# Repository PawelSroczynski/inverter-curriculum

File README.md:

# From Zero Electronics to Community Energy Independence

**Build droop-controlled inverters. Connect them into a tiered AC swarm grid.**

Learn electronics from scratch, build 6-15kW inverters, connect them into a self-organizing microgrid that powers your whole community—no utility required.

---

## Why Build This?

| Problem | This Project |
|---------|--------------|
| Commercial inverters cost $3,000+ each | Build for ~$775 per unit |
| Proprietary systems, no repair possible | Open source, fully repairable |
| Single inverter = single point of failure | Swarm shares load automatically |
| Grid dependency | Complete energy independence |
| Complex microgrid controllers | Self-organizing via droop control |

**End Goal:** 12-household swarm microgrid with 72kW capacity, tiered AC buses, automatic power sharing between clusters.

---

## System Architecture

The system uses a **tiered AC bus** design: each cluster has its own internal bus, and clusters connect through a separate swarm bus via gateways. This means only 3 gateways need to sync—not 12 inverters.

---

### Level 1: Tiered Bus Overview

```
┌──────────────────────────────────────────────────────────────────────────────────────┐
│                              SWARM BUS (1000m backbone)                              │
│                                                                                      │
│      ════════════════════════════════════════════════════════════════════════        │
│           │                         │                         │                      │
│      ┌────┴────┐               ┌────┴────┐               ┌────┴────┐                │
│      │GATEWAY A│               │GATEWAY B│               │GATEWAY C│                │
│      │Contactor│               │Contactor│               │Contactor│                │
│      │  ESP32  │               │  ESP32  │               │  ESP32  │                │
│      └────┬────┘               └────┬────┘               └────┬────┘                │
│           │                         │                         │                      │
│      ═════╪═════               ═════╪═════               ═════╪═════                │
│      CLUSTER A                 CLUSTER B                 CLUSTER C                  │
│      INTERNAL BUS              INTERNAL BUS              INTERNAL BUS               │
│      (80m)                     (80m)                     (80m)                       │
│           │                         │                         │                      │
│      ┌────┼────┐               ┌────┼────┐               ┌────┼────┐                │
│      │    │    │               │    │    │               │    │    │                │
│     H1   H2   H3  H4          H5   H6   H7  H8          H9  H10  H11 H12            │
│     INV  INV  INV INV         INV  INV  INV INV         INV  INV  INV INV           │
│                                                                                      │
│    ◄──────────────────────── 1000m total site ───────────────────────────►          │
│                                                                                      │
│    KEY BENEFIT: Only 3 gateways sync on swarm bus, not 12 inverters                 │
│                                                                                      │
│    TWO LEVELS OF DROOP:                                                             │
│    • Within cluster: 4 inverters share via droop on internal bus                    │
│    • Between clusters: 3 gateways share via droop on swarm bus                      │
│                                                                                      │
└──────────────────────────────────────────────────────────────────────────────────────┘
```

---

### Self-Reliance Levels

The system operates in 4 modes, from most isolated to most connected:

```
┌──────────────────────────────────────────────────────────────────────────────────────┐
│  LEVEL 1: HOUSE SELF-RELIANT (99% of time)                                          │
│                                                                                      │
│    House 1: [Solar] → [Battery] → [Inverter] → [Loads]                              │
│             Own production covers own consumption                                    │
│             No power flows to/from cluster bus                                       │
│                                                                                      │
├──────────────────────────────────────────────────────────────────────────────────────┤
│  LEVEL 2: CLUSTER SELF-RELIANT (swarm disconnected)                                 │
│                                                                                      │
│    Cluster A: H1 ←→ H2 ←→ H3 ←→ H4                                                  │
│               Sharing within cluster via droop                                       │
│               Gateway contactor: OPEN (isolated from swarm)                          │
│                                                                                      │
│    Use case: Swarm bus fault, or cluster has enough internal capacity               │
│                                                                                      │
├──────────────────────────────────────────────────────────────────────────────────────┤
│  LEVEL 3: CLUSTER NEEDS HELP (normal swarm operation)                               │
│                                                                                      │
│    Cluster A (depleted) ←── power ←── Cluster B (surplus)                           │
│                                             │                                        │
│    Gateway A closes contactor when:         │                                        │
│    • Cluster A frequency drops (heavy load) │                                        │
│    • Swarm frequency is higher (others OK)  │                                        │
│    • Frequencies match within ±0.5Hz        │                                        │
│                                                                                      │
├──────────────────────────────────────────────────────────────────────────────────────┤
│  LEVEL 4: HOUSE NEEDS HELP (within cluster)                                         │
│                                                                                      │
│    H1 (heavy load, e.g. EV) ←── power ←── H2, H3, H4 (light loads)                  │
│                                                                                      │
│    Via droop physics on cluster internal bus                                         │
│    No gateway involved - stays within cluster                                        │
│                                                                                      │
└──────────────────────────────────────────────────────────────────────────────────────┘
```

---

### Inter-Cluster Power Flow

How power moves from House 11 (Cluster C) to House 1 (Cluster A):

```
    H11 Inverter (50.0 Hz, light load)
            │
            ↓ power flows
    Cluster C Internal Bus
            │
            ↓
    Gateway C (contactor closed)
            │
            ↓
    ═══════ SWARM BUS ═════════════════════════════
            │
            ↓
    Gateway A (contactor closed)
            │
            ↓
    Cluster A Internal Bus (49.5 Hz, heavy load)
            │
            ↓ power flows
    H1 Inverter
            │
            ↓
    H1 Loads (kettle, EV, etc.)

    5 HOPS, PURE PHYSICS:
    No direct communication between H1 and H11.
    Power flows automatically from high frequency (surplus)
    to low frequency (deficit) via droop control.
```

---

### Gateway Sync Logic

Each gateway monitors both bus frequencies and decides when to connect:

```
    ┌─────────────────────────────────────────────────────────────────┐
    │  GATEWAY DECISION FLOWCHART                                     │
    │                                                                 │
    │  [Measure cluster frequency] → f_cluster                        │
    │  [Measure swarm frequency]   → f_swarm                          │
    │                                                                 │
    │  IF |f_cluster - f_swarm| < 0.5 Hz:                             │
    │      → CLOSE contactor (safe to connect)                        │
    │                                                                 │
    │  ELSE IF f_cluster < f_swarm - 0.5:                             │
    │      → Cluster needs power, wait for freq match                 │
    │                                                                 │
    │  ELSE IF f_cluster > f_swarm + 0.5:                             │
    │      → Cluster has surplus, wait for freq match                 │
    │                                                                 │
    │  IF f_cluster < 47.5 Hz:                                        │
    │      → EMERGENCY: cluster critically low                        │
    │      → Force close (accept brief surge)                         │
    │                                                                 │
    └─────────────────────────────────────────────────────────────────┘
```

---

### Level 2: Cluster Internal Detail

Each house is self-reliant with 6-15kW inverter. Load-balancing only kicks in for special scenarios.

```
┌──────────────────────────────────────────────────────────────────────────────────────┐
│                      CLUSTER - NORMAL OPERATION (99% of the time)                    │
│                                                                                      │
│   HOUSE 1                  HOUSE 2                  HOUSE 3                          │
│   ┌──────────────────┐     ┌──────────────────┐     ┌──────────────────┐            │
│   │ Solar 6kW        │     │ Solar 6kW        │     │ Solar 6kW        │            │
│   │ Bat 15kWh        │     │ Bat 15kWh        │     │ Bat 15kWh        │            │
│   │ Inv 6kW          │     │ Inv 6kW          │     │ Inv 6kW          │            │
│   │                  │     │                  │     │                  │            │
│   │ BATTERY 48V      │     │ BATTERY 48V      │     │ BATTERY 48V      │            │
│   │      │           │     │      │           │     │      │           │            │
│   │      ▼           │     │      ▼           │     │      ▼           │            │
│   │ INVERTER 50.0Hz  │     │ INVERTER 50.0Hz  │     │ INVERTER 50.0Hz  │            │
│   │      │           │     │      │           │     │      │           │            │
│   │      ▼           │     │      ▼           │     │      ▼           │            │
│   │ LOADS 2kW        │     │ LOADS 4kW        │     │ LOADS 1kW        │            │
│   │ (fridge,lights)  │     │ (oven,fridge)    │     │ (lights,TV)      │            │
│   └────────┼─────────┘     └────────┼─────────┘     └────────┼─────────┘            │
│            │                        │                        │                      │
│   ─────────┴────────────────────────┴────────────────────────┴───────────────►      │
│   230V AC BUS @ 50.0 Hz - NO POWER FLOWING BETWEEN HOUSES (each self-sufficient)    │
│   ──────────────────────────────────────────────────────────────────► to cluster    │
│                                                                                      │
│            │ RJ45                   │ RJ45                   │ RJ45                 │
│   ─────────○───────────────────────○───────────────────────○────────► to cluster   │
│   CAN BUS: sync timing + SOC% + status data                                         │
│                                                                                      │
│   NORMAL: Each 6kW inverter handles its own loads easily (oven=3kW, fridge=200W)    │
│                                                                                      │
└──────────────────────────────────────────────────────────────────────────────────────┘

┌──────────────────────────────────────────────────────────────────────────────────────┐
│                  CLUSTER - SPECIAL SCENARIO: EV CHARGING EXCEEDS 6kW                 │
│                                                                                      │
│   HOUSE 1                  HOUSE 2 (needs help!)   HOUSE 3                          │
│   ┌──────────────────┐     ┌──────────────────┐     ┌──────────────────┐            │
│   │ Inv 6kW          │     │ Inv 6kW (MAXED)  │     │ Inv 6kW          │            │
│   │                  │     │                  │     │                  │            │
│   │ BATTERY 48V      │     │ BATTERY 48V      │     │ BATTERY 48V      │            │
│   │      │           │     │      │           │     │      │           │            │
│   │      ▼ 2kW       │     │      ▼ 6kW MAX   │     │      ▼ 1.5kW     │            │
│   │ INVERTER 50.0Hz  │     │ INVERTER 49.7Hz  │     │ INVERTER 49.9Hz  │            │
│   │      │           │     │      │           │     │      │           │            │
│   │      ▼           │     │      ▼           │     │      ▼           │            │
│   │ LOADS 1kW        │     │ LOADS 7kW !!!    │     │ LOADS 1kW        │            │
│   │                  │     │ (EV charger)     │     │                  │            │
│   └────────┼─────────┘     └────────┼─────────┘     └────────┼─────────┘            │
│            │                        │                        │                      │
│   ─────────┴────────────────────────┴────────────────────────┴───────────────►      │
│                                                                                      │
│            ════1.0kW═══════════════►║◄════════0.5kW══════════                       │
│                    House 1 pushes   ║   House 3 pushes                              │
│                                                                                      │
│   230V AC BUS @ 49.85 Hz - POWER FLOWS TO HOUSE 2 (droop triggered)                 │
│   ──────────────────────────────────────────────────────────────────► to cluster    │
│                                                                                      │
├──────────────────────────────────────────────────────────────────────────────────────┤
│   WHY LOAD-BALANCING KICKS IN:                                                      │
│                                                                                      │
│   House 2 plugs in EV charger (7kW) but inverter maxes at 6kW:                       │
│   • Inverter strains → frequency drops to 49.7 Hz                                   │
│   • House 1 & 3 see low freq → push power to bus                                    │
│   • House 2 gets: 6kW local + 1kW from H1 + 0.5kW from H3 = 7.5kW available         │
│                                                                                      │
│   OTHER SCENARIOS THAT TRIGGER SHARING:                                             │
│   • Low battery (BMS limits output) → neighbors supply deficit                      │
│   • Inverter fault/maintenance → house runs entirely from bus                       │
│   • Motor startup surge (9kW for 2 sec) → cluster absorbs spike                     │
│                                                                                      │
└──────────────────────────────────────────────────────────────────────────────────────┘
```

---

### Level 3: House Detail

Internal wiring of one house, showing connection to cluster AC bus.

```
┌────────────────────────────────────────────────────────────────────────────────────┐
│                              HOUSE (typical)                                       │
│                                                                                    │
│   ROOF                                                                             │
│   ┌──────────────────┐                                                             │
│   │   Solar Panels   │                                                             │
│   │      3kW         │                                                             │
│   └────────┬─────────┘                                                             │
│            │ DC (Vmp ~100V)                                                        │
│            ▼                                                                       │
│   ┌──────────────────┐                                                             │
│   │   MPPT Charger   │                                                             │
│   │  (Libre Solar)   │                                                             │
│   └────────┬─────────┘                                                             │
│            │ 48V DC                                                                │
│            ▼                                                                       │
│   ┌──────────────────┐                                                             │
│   │       BMS        │   48V DC stays inside this house                            │
│   │   48V / 15kWh    │   (no DC connection to other houses)                        │
│   │    LiFePO4       │                                                             │
│   └────────┬─────────┘                                                             │
│            │ 48V DC                                                                │
│            ▼                                                                       │
│   ┌──────────────────┐              ┌──────────────────────────────────────────┐   │
│   │    INVERTER      │     RJ45     │                                          │   │
│   │      6kW         │◄────────────►│  CAN BUS                                 │   │
│   │    EG8010        │              │  ◄───── to/from other houses + clusters  │   │
│   │    ESP32         │              └──────────────────────────────────────────┘   │
│   │    MCP2515       │                                                             │
│   │  (MASTER/SLAVE)  │                                                             │
│   └────────┬─────────┘                                                             │
│            │ 230V AC                                                               │
│            ▼                                                                       │
│   ┌──────────────────┐              ┌──────────────────────────────────────────┐   │
│   │   MAIN BREAKER   │    63A MCB   │                                          │   │
│   │   (house entry)  │◄────────────►│  230V AC CLUSTER BUS                     │   │
│   └────────┬─────────┘              │  ◄───── to/from other houses + clusters  │   │
│            │                        └──────────────────────────────────────────┘   │
│            │                                                                       │
│   ═════════╧═══════════════════════════════════════════════════════════            │
│   ║            230V AC HOUSE DISTRIBUTION BOARD                    ║               │
│   ══════╤══════════╤══════════╤══════════╤══════════╤══════════════                │
│         │          │          │          │          │                              │
│      ┌──┴──┐    ┌──┴──┐    ┌──┴──┐    ┌──┴──┐    ┌──┴──┐                          │
│      │ 6A  │    │ 10A │    │ 16A │    │ 16A │    │ 20A │                          │
│      │Light│    │Fridge│   │Plugs│    │Plugs│    │Oven │                          │
│      │ MCB │    │ MCB │    │ MCB │    │ MCB │    │ MCB │                          │
│      └──┬──┘    └──┬──┘    └──┬──┘    └──┬──┘    └──┬──┘                          │
│         │          │          │          │          │                              │
│         ▼          ▼          ▼          ▼          ▼                              │
│      Lights     Fridge     Kitchen    Living     Oven                              │
│                            plugs      plugs                                        │
│                                                                                    │
│   CONNECTION DETAIL: How House Connects to Cluster                                 │
│   ┌────────────────────────────────────────────────────────────────────────────┐   │
│   │                                                                            │   │
│   │    230V AC CLUSTER BUS (shared with other houses)                          │   │
│   │    ═══════════════╤═══════════════════════════════════════                 │   │
│   │                   │                                                        │   │
│   │              ┌────┴────┐                                                   │   │
│   │              │  63A    │  Main breaker: isolates house from cluster        │   │
│   │              │ BREAKER │  if fault or maintenance                          │   │
│   │              └────┬────┘                                                   │   │
│   │                   │                                                        │   │
│   │    ═══════════════╧═══════════════════════════════════════                 │   │
│   │    230V AC HOUSE DISTRIBUTION (internal to this house)                     │   │
│   │                                                                            │   │
│   │    Power flows BOTH directions:                                            │   │
│   │    • House produces excess → pushes to cluster bus → other houses use it   │   │
│   │    • House needs more → pulls from cluster bus → other houses supply it    │   │
│   │                                                                            │   │
│   │    ONLY TWO CONNECTIONS LEAVE THIS HOUSE:                                  │   │
│   │    1. 230V AC (L + N + PE) → to cluster AC bus                             │   │
│   │    2. CAN bus (RJ45) → to other houses for communication                   │   │
│   │                                                                            │   │
│   │    48V DC stays entirely inside the house (battery is isolated)            │   │
│   │                                                                            │   │
│   └────────────────────────────────────────────────────────────────────────────┘   │
│                                                                                    │
└────────────────────────────────────────────────────────────────────────────────────┘
```

---

### Hardware Summary

**Per House (isolated 48V DC system):**
| Component | Description |
|-----------|-------------|
| Solar Panels | 3kW array (size varies) |
| MPPT Charger | Libre Solar MPPT-2420-HC or similar |
| BMS + Battery | Libre Solar BMS-C1 + 48V/15kWh LiFePO4 (stays inside house) |
| Inverter | OzInverter 6kW with EG8010 + ESP32 + MCP2515 |
| Main Breaker | 63A MCB, isolates house from cluster AC bus |
| RJ45 Jack | CAN bus connection to other houses |

**Per Cluster (shared between houses):**
| Component | Description |
|-----------|-------------|
| 230V AC Bus | 4mm² cable connecting all house inverter outputs (10-30m) |
| CAN Bus | RJ45 cables daisy-chaining all houses (10-30m runs) |

**Per Gateway (connects cluster to swarm bus):**
| Component | Description |
|-----------|-------------|
| Gateway ESP32 | Monitors both bus frequencies, controls contactor |
| Contactor 63A | Connects/disconnects cluster from swarm bus |
| Voltage sensors | Measures cluster and swarm bus frequencies |

**Swarm Bus (between clusters):**
| Component | Description |
|-----------|-------------|
| 5-Wire Cable | L + N + PE (4mm²) + CAN-H + CAN-L (0.5mm²) |
| Distance | 200-400m between gateways |

---

### How It Works

**Power Flow (tiered):**
1. Sun → Solar panels → MPPT → Battery (48V DC, inside house)
2. Battery → Inverter → 230V AC → House loads
3. Excess → Cluster internal bus → Other houses in cluster (via droop)
4. Still excess → Gateway → Swarm bus → Other clusters (via droop)

**No DC Bus Between Houses:**
- Each house has isolated 48V battery (simpler, cheaper wiring)
- Power sharing happens via 230V AC (thinner cables for same power)
- Battery balancing is indirect: low battery house draws from AC, others supply

**Communication:**
1. ESP32 master broadcasts sync timing @ 100Hz on CAN bus
2. All slave ESP32s adjust their EG8010 phase to match
3. Status messages (SOC%, load, faults) shared via ThingSet protocol

**Droop Control (automatic power sharing):**
- Heavy load → inverter frequency drops slightly (e.g., 50.0 → 49.8 Hz)
- Other inverters sense lower frequency → push more power
- No central controller needed - physics handles balancing

```
How Droop Control Shares Power Between Houses (EV Charging Example):

  House 2 (charging EV at 7kW)           House 1 (light load - 1kW)
  ┌─────────────────────────────┐        ┌─────────────────────────────┐
  │  6kW inverter (maxed out)   │        │  6kW inverter (idle)        │
  │                             │        │                             │
  │  Battery ──► Inverter ──┬──►│ EV     │  Battery ──► Inverter ──┬──►│ load
  │    48V        6kW       │   │ 7kW    │    48V        2kW       │   │ 1kW
  │              49.7 Hz    │   │        │              50.0 Hz    │   │
  └─────────────────────────┼───┘        └─────────────────────────┼───┘
                            │                                      │
                ◄═══════════╧══════════════════════════════════════╧═══
                230V AC BUS - House 1 pushes 2kW → House 2 (freq settles at 49.85 Hz)

  WHY THIS TRIGGERS SHARING (with 6kW inverters):
  • House 2 needs 7kW but its inverter maxes out at 6kW
  • Inverter strains → frequency drops to 49.7 Hz
  • House 1 sees low freq → pushes power to help

  1. House 2 plugs in EV charger (7kW) → inverter hits 6kW limit → freq drops
  2. House 1 inverter sees 49.7 Hz → increases output → pushes power to bus
  3. Power flows: House 1 battery → inverter → AC bus → House 2 EV
  4. System settles at 49.85 Hz with 7kW delivered

  The math for House 2:
  • EV charger needs:         7.0 kW
  • Local 6kW inverter maxed: 6.0 kW (can't do more)
  • AC bus supplies:          1.0 kW (from House 1)
  • House 1 also powers own:  1.0 kW load
  • House 1 total output:     2.0 kW (1kW local + 1kW to bus)

  Key: Single inverter can't do 7kW, but cluster of two 6kW inverters can.
       Droop control automatically shares the load - no manual switching.
```

---

### When AC Bus Power Sharing Kicks In

With 6-15kW inverters, normal household loads won't trigger sharing. The real value is resilience:

```
┌─────────────────────────────────────────────────────────────────────────────┐
│  SCENARIO 1: Low Battery Protection                                        │
│                                                                             │
│  House 2: SOC at 15% → BMS limits discharge to 1kW                          │
│  House 2 load: 3kW (fridge + pump + lights)                                 │
│  ───────────────────────────────────────────────────────────────            │
│  House 1 & 3 push 2kW through AC bus → House 2 stays powered                │
│                                                                             │
├─────────────────────────────────────────────────────────────────────────────┤
│  SCENARIO 2: Inverter Failure / Maintenance                                 │
│                                                                             │
│  House 2: Inverter offline (fault or repair)                                │
│  House 2 loads: still connected to AC bus via breaker                       │
│  ───────────────────────────────────────────────────────────────            │
│  House 1 & 3 supply House 2 entirely → no blackout during repair            │
│                                                                             │
├─────────────────────────────────────────────────────────────────────────────┤
│  SCENARIO 3: Uneven Solar (shade, orientation, dust)                        │
│                                                                             │
│  Morning: House 1 (east panels) has full sun, House 3 (west) has none       │
│  Evening: reversed                                                          │
│  ───────────────────────────────────────────────────────────────            │
│  Power flows from sunny house → saves battery cycles across cluster         │
│                                                                             │
├─────────────────────────────────────────────────────────────────────────────┤
│  SCENARIO 4: Big Transient Loads (motor startup, welder)                    │
│                                                                             │
│  House 2: Starts 3kW water pump (startup surge 9kW for 2 seconds)           │
│  Single 6kW inverter might trip on overcurrent                              │
│  ───────────────────────────────────────────────────────────────            │
│  AC bus absorbs surge → all three inverters share the spike                 │
│                                                                             │
├─────────────────────────────────────────────────────────────────────────────┤
│  SCENARIO 5: EV Charging / Heavy Scheduled Loads                            │
│                                                                             │
│  House 2 wants to charge EV at 7kW                                          │
│  Their 6kW inverter can't do it alone                                       │
│  ───────────────────────────────────────────────────────────────            │
│  Neighbor's excess solar flows through AC bus → 7kW charging possible       │
│                                                                             │
└─────────────────────────────────────────────────────────────────────────────┘
```

The AC bus is **community resilience** - nobody goes dark because of one failure.

---

### Swarm Capacity at Scale

What happens when you connect more houses and clusters:

**Per house baseline:**
- Inverter: 6-15 kW
- Solar: 6 kW
- Battery: 15 kWh

| Scale | Houses | Inverter Capacity | Solar | Battery Storage |
|-------|--------|-------------------|-------|-----------------|
| Single house | 1 | 6-15 kW | 6 kW | 15 kWh |
| **Cluster (4 houses)** | 4 | 24-60 kW | 24 kW | 60 kWh |
| **Swarm (12 houses)** | 12 | 72-180 kW | 72 kW | 180 kWh |

**What 72-180 kW powers simultaneously:**

```
72 kW (minimum swarm config):
├── 12× electric ovens (3kW each)
├── 3× EV chargers (7kW each)
├── 24× washing machines running at once
├── or one small workshop (welders + compressors)

180 kW (maximum swarm config):
├── Small factory level power
├── Community event (PA, lights, food trucks)
├── Emergency shelter for 50+ people
```

**Battery perspective (15 kWh per house):**

```
Typical day:
  Night consumption (16h): ~5 kWh
  15 kWh battery = 3 nights reserve

Cloudy winter day:
  Solar produces: ~2 kWh (vs 6 kWh normal)
  Consumption: 10 kWh
  Deficit: 8 kWh → covered by battery, still 7 kWh left

3 consecutive cloudy days:
  Deficit: 8 kWh × 3 = 24 kWh per house
  15 kWh battery alone: NOT ENOUGH
  But cluster sharing helps: sunny neighbor covers your deficit

180 kWh swarm total:
  Community event (5 hours × 20 kW): 100 kWh → still 80 kWh reserve
  Winter evening peak (all cooking): 40 kW for 2h = 80 kWh → covered
```

The swarm becomes a **small village grid** - completely independent from utility.

---

### Connecting High-Power Loads (>6kW)

Single house inverter maxes at 6kW. For larger loads, connect directly to cluster or swarm bus.

**Where to connect based on load size:**

| Load Power | Connect To | Why |
|------------|------------|-----|
| <6kW | House breaker | Single inverter handles it |
| 6-24kW | Cluster bus | 4 inverters share (24kW max) |
| 24-72kW | Swarm bus | All 12 inverters share |

**Connection point for high-power equipment:**

```
CLUSTER BUS ════════════════════════════════════════
     │           │           │           │
   House1      House2      House3      HIGH-POWER
   6kW inv     6kW inv     6kW inv     EQUIPMENT
                                       (connects here,
                                        not through house)
```

---

### Energy Accumulation Through Work

**Key insight:** On sunny days, use surplus power for work that stores energy in other forms.

Instead of filling batteries (limited capacity), convert solar abundance into:
- **Processed materials** (wood chips, grain, crushed stone)
- **Pumped water** (irrigation tanks, elevated storage)
- **Compressed air** (workshop tanks)
- **Heated mass** (water tanks, thermal storage)
- **Charged vehicles** (EVs, e-bikes, tractors)

**Seasonal high-power tasks (best done on sunny days):**

```
┌─────────────────────────────────────────────────────────────────────────┐
│  TASK                      │ POWER  │ CONNECT TO  │ ENERGY STORED AS   │
├────────────────────────────┼────────┼─────────────┼────────────────────┤
│  Wood chipper              │ 15-25kW│ Cluster bus │ Processed firewood │
│  Grain mill                │ 5-15kW │ Cluster bus │ Flour/feed         │
│  Water pump to hill tank   │ 3-10kW │ House/Clust │ Potential energy   │
│  Air compressor (big tank) │ 5-10kW │ Cluster bus │ Compressed air     │
│  EV fast charging          │ 7-22kW │ Cluster bus │ Vehicle range      │
│  Electric cement mixer     │ 2-5kW  │ House       │ Built structure    │
│  Welding (construction)    │ 5-15kW │ Cluster bus │ Built structure    │
│  Water heater (big tank)   │ 3-6kW  │ House       │ Hot water          │
│  Freezer loading (harvest) │ 1-3kW  │ House       │ Preserved food     │
└─────────────────────────────────────────────────────────────────────────┘
```

**Example: Wood chipping day**

```
Sunny summer day, 11:00-15:00 (peak solar)

Solar production:    ~50kW (not all panels at perfect angle)
Baseline house loads: -12kW
Wood chipper:        -20kW
─────────────────────────────────────
Net:                 +18kW → batteries charging

Result: 4 hours × 20kW = 80kWh of work
        = 4 cubic meters of wood chips
        = heating fuel for 2 weeks of winter

The sun's energy is now stored as processed firewood,
not limited by battery capacity.
```

**Scheduling principle:**
- Heavy processing → sunny midday
- Light tasks → morning/evening
- Storage tasks (freezing, heating water) → whenever surplus
- Construction/welding → plan around weather forecast

This turns the microgrid into a **productive community tool**, not just household power.

---

### Monitoring Layer (Home Assistant)

*Home Assistant dashboard concept: Swarm grid monitoring showing clusters, power flow, and cell health*

The microgrid has two control layers with different responsibilities:

| Layer | Tool | Response Time | Purpose |
|-------|------|---------------|---------|
| **Hard** | Inverter/BMS firmware | <1ms | Droop control, protection, contactor |
| **Soft** | Home Assistant | seconds | Dashboards, logging, alerts, analysis |

**Keep in firmware (hard layer):**
- Droop frequency control
- Protection disconnects
- Contactor decisions
- Cell balancing

**Good for Home Assistant (soft layer):**
- SOC monitoring across all 12 houses
- Energy production/consumption dashboards
- Cell imbalance alerts
- Historical data and trends
- AI-assisted failure analysis

**Integration points:**

| Device | HA Integration |
|--------|----------------|
| NEEY balancer | Bluetooth via ESPHome |
| JK BMS | [esphome-jk-bms](https://github.com/syssi/esphome-jk-bms) |
| ENNOID BMS | CAN → ESP32 → HA |
| Inverter ESP32 | MQTT / CAN → WiFi bridge |

**AI-assisted configuration:**
[HA Vibecode Agent](https://github.com/Coolver/home-assistant-vibecode-agent) enables natural language Home Assistant configuration via Claude Code MCP integration.

**Deep logging and debugging:**
See [LOGGING.md](LOGGING.md) for the 3-tier logging architecture with local house logs, cluster aggregation, and AI-powered failure analysis.

---

## Practical Droop Control Experiments

These hands-on experiments let you discover how droop control works. Each builds on the previous.

### Equipment Needed

| Item | Purpose | Cost |
|------|---------|------|
| Frequency counter or multimeter with Hz | Measure bus frequency | $20-50 |
| Clamp ammeter (AC) | Measure individual currents | $30-50 |
| Kill-A-Watt or power meter | Measure load power | $20-30 |
| Oscilloscope (optional) | See waveforms, phase | $50-300 |
| Variable load (heaters, bulbs) | Create controlled loads | $50-100 |
| 10Ω 100W power resistors | Current limiting for safety | $10-20 |

---

### Experiment 1: Single Inverter Frequency vs Load

**Goal:** Verify YOUR inverter drops frequency under load (droop characterization)

```
SETUP:
                    ┌─────────────┐
   BATTERY ────────►│  INVERTER   │────────► VARIABLE LOAD
   48V              │  (your DIY) │          (light bulbs/heater)
                    └──────┬──────┘
                           │
                    ┌──────┴──────┐
                    │ FREQUENCY   │
                    │ METER       │
                    └─────────────┘

PROCEDURE:
1. No load: Record frequency = _______ Hz (should be ~50.0)
2. Add 500W: Record frequency = _______ Hz
3. Add 1000W: Record frequency = _______ Hz
4. Continue to 3kW: Record frequency = _______ Hz

EXPECTED (with 3% droop, k=0.25 Hz/kW):
  Load        Frequency
  0W          50.00 Hz
  500W        49.88 Hz
  1000W       49.75 Hz
  2000W       49.50 Hz
  3000W       49.25 Hz

WHAT YOU LEARN:
  ✓ Your droop coefficient matches your code
  ✓ The relationship is linear
  ✓ Frequency = system load indicator
```

---

### Experiment 2: Two Inverters, First Parallel Connection

**Goal:** Watch two inverters find common frequency automatically

```
SETUP:
                         SWITCH (open initially)
                              ○
   INVERTER A ───────────────╱─────────────── INVERTER B
       │                                           │
       ▼                                           ▼
   FREQ METER A                               FREQ METER B

   LOAD A: 1kW                                LOAD B: 0kW

PROCEDURE:
1. Start both inverters separately (switch OPEN)
2. Measure: Freq A = _____ Hz, Freq B = _____ Hz
   (A should be ~49.75 Hz, B should be ~50.0 Hz)

3. CLOSE THE SWITCH (connect them together)

4. Watch frequencies converge!
   After 1 sec: Freq A = _____, Freq B = _____
   After 5 sec: Both should be ~49.87 Hz

5. Measure current in connecting wire: _____ A
   This current IS the power transfer!

EXPECTED:
  Before: A=49.75 Hz (loaded), B=50.0 Hz (unloaded)
  After:  Both≈49.87 Hz, each supplies ~0.5kW

WHAT YOU LEARN:
  ✓ Inverters find common frequency automatically
  ✓ Load balances without commands
  ✓ You SEE droop control working!
```

---

### Experiment 3: Unequal Loading, Equal Sharing

**Goal:** Prove droop shares load equally regardless of WHERE load connects

```
SETUP:
   INVERTER A ══════════════════════════ INVERTER B
       │                                      │
       ▼                                      ▼
   AMMETER A                              AMMETER B
       │                                      │
       └──────────────┬───────────────────────┘
                      │
                      ▼
                  LOAD (2kW)
                  (connected to A's side ONLY)

PROCEDURE:
1. Connect 2kW load to Inverter A's terminals only
2. Measure:
   - Current from A: _____ A
   - Current from B: _____ A
   - Bus frequency: _____ Hz

EXPECTED:
  Current A: ~4.3A (≈1kW)
  Current B: ~4.3A (≈1kW)
  Frequency: ~49.75 Hz

  Even though load is physically at A,
  BOTH inverters supply equal power!

WHAT YOU LEARN:
  ✓ Load location doesn't matter
  ✓ Droop balances automatically
  ✓ No complex load management needed
```

---

### Experiment 4: Droop Mismatch (What NOT to Do)

**Goal:** Experience instability when droop coefficients don't match

```
SETUP:
   INVERTER A ═══════════════════ INVERTER B
   k = 0.25 Hz/kW                 k = 0.5 Hz/kW (DIFFERENT!)

   Shared load: 2kW

PROCEDURE:
1. Set different droop coefficients
2. Connect together with shared load
3. Watch/listen for oscillation:
   - Frequency hunting (±0.2 Hz swings)
   - Audible hum changing pitch
   - Current swinging back and forth

4. Change B's droop to match A's (k = 0.25)
5. Oscillation should stop

EXPECTED:
  Mismatched: Unstable, hunting, buzzing
  Matched: Stable, quiet, steady

WHAT YOU LEARN:
  ✓ ALL inverters must have IDENTICAL droop
  ✓ Mismatch causes fighting
  ✓ Calibration is critical
```

---

### Experiment 5: Phase Mismatch Danger (LOW POWER ONLY!)

**Goal:** Understand why sync matters - observe circulating current

```
⚠️ WARNING: Use current-limiting resistor! Can damage inverters!

SETUP:
   INVERTER A ────[10Ω RESISTOR]──── INVERTER B
   (50.0 Hz)      (limits current!)   (50.0 Hz)
       │                                  │
   Manually set                       Keep at
   to 50.1 Hz                         50.0 Hz

PROCEDURE:
1. Set A to 50.1 Hz, B to 50.0 Hz (0.1 Hz difference)
2. Connect through 10Ω power resistor
3. Measure current through resistor: _____ A

4. Increase A to 50.2 Hz: Current = _____ A
5. Increase A to 50.5 Hz: Current = _____ A

EXPECTED:
  0.1 Hz diff: ~0.5A circulating
  0.2 Hz diff: ~1.0A circulating
  0.5 Hz diff: ~2-3A circulating

WHAT YOU LEARN:
  ✓ Frequency difference = circulating current
  ✓ Without resistor, current would be DESTRUCTIVE
  ✓ Why CAN sync matters for tight parallel
```

---

### Experiment 6: Four Inverter Cluster

**Goal:** Verify full cluster load sharing works

```
SETUP:
   INV1 ═══╤═══ INV2
          │
   BUS ═══╪═══════════════
          │
   INV3 ═══╧═══ INV4

   Variable loads (heaters, bulbs)

MEASUREMENT TABLE:

Test   Total    Bus      I₁     I₂     I₃     I₄     Equal?
       Load     Freq
────   ─────    ────     ──     ──     ──     ──     ──────
1      0kW      ____     __     __     __     __
2      4kW      ____     __     __     __     __     ~1kW each?
3      8kW      ____     __     __     __     __     ~2kW each?
4      12kW     ____     __     __     __     __     ~3kW each?
5*     8kW      ____     __     __     __     __     Still equal?

* Test 5: All 8kW load connected to INV1's terminals only

EXPECTED:
  All currents approximately equal in EVERY test
  Bus frequency drops as total load increases

WHAT YOU LEARN:
  ✓ 4-way sharing works
  ✓ Load location irrelevant
  ✓ System scales predictably
```

---

### Experiment 7: Master Failure & Recovery

**Goal:** Test that system survives master ESP32 failure

```
SETUP:
   INV1 (MASTER) ═══════ INV2 (SLAVE)
        │                    │
   CAN bus connecting all    │
        │                    │
   INV3 (SLAVE) ═══════ INV4 (SLAVE)

   Shared load: 8kW running

PROCEDURE:
1. System running, INV1 is master, 8kW load
2. Note: Each inverter supplies ~2kW
3. UNPLUG INV1's POWER (simulate failure)
4. Start timer - measure:
   - Lights flicker? How long? _____ ms
   - Do INV2/3/4 keep running? Y/N
   - Does new master emerge? Y/N
   - New steady state: ___ kW each (should be ~2.67kW)
5. Time to stable operation: _____ ms

EXPECTED:
  - Brief disturbance (<200ms)
  - One of INV2/3/4 becomes master
  - System continues at reduced capacity
  - Load still served (now 2.67kW each)

WHAT YOU LEARN:
  ✓ Master election works
  ✓ No single point of failure
  ✓ Graceful degradation
```

---

### Experiment 8: 80m Cable Power Transfer

**Goal:** Measure actual droop sharing over realistic distance

```
SETUP:
   INVERTER A ═══[80m cable]═══ INVERTER B
   House 1                      House 2
       │                            │
   No load                      3kW load

PROCEDURE:
1. INV B has 3kW load, INV A has no load
2. Start both, let system stabilize
3. Measure:
   - Bus frequency: _____ Hz
   - Current from A: _____ A (power to bus)
   - Current from B: _____ A (power to load)
   - Voltage at A: _____ V
   - Voltage at B: _____ V (should be slightly lower)

4. Calculate:
   - Power from A: _____ W
   - Power from B: _____ W
   - Voltage drop in cable: _____ V
   - Cable loss: _____ W

EXPECTED (4mm² cable, 80m):
  Frequency: ~49.63 Hz
  A supplies: ~1.5kW
  B supplies: ~1.5kW
  Voltage drop: ~5-10V (2-4%)
  Cable loss: ~50-100W (acceptable)

WHAT YOU LEARN:
  ✓ Real-world sharing works
  ✓ Cable loss is measurable but acceptable
  ✓ Distance doesn't prevent sharing
```

---

### Calibration Procedure (Required Before Parallel Operation)

**Every inverter must have matched droop coefficient:**

```
CALIBRATION STEPS:

1. REFERENCE INVERTER (INV1):
   - Apply exactly 3kW load
   - Measure frequency: _____ Hz
   - Calculate actual k: k = (50.0 - f) / 3.0 = _____ Hz/kW

2. TEST INVERTER (INV2):
   - Apply exactly 3kW load
   - Measure frequency: _____ Hz
   - If different from INV1, adjust code:

     // Adjust this value until frequencies match
     #define DROOP_K  0.25  // Change until INV2 matches INV1

3. VERIFICATION:
   - Both at 3kW: Freq should be within ±0.02 Hz
   - Connect together: Should be stable, no oscillation

4. REPEAT for INV3, INV4, etc.

RECORD YOUR CALIBRATION:
  INV1: k = _____ Hz/kW (reference)
  INV2: k = _____ Hz/kW (adjusted to match)
  INV3: k = _____ Hz/kW (adjusted to match)
  INV4: k = _____ Hz/kW (adjusted to match)
```

---

### The Droop Control Formula

```
┌─────────────────────────────────────────────────────────────────┐
│                                                                 │
│   f = 50.0 - (k × P)                                            │
│                                                                 │
│   f = output frequency (Hz)                                     │
│   k = droop coefficient (recommend 0.25 Hz/kW for DIY)          │
│   P = power output (kW)                                         │
│                                                                 │
│   Example with k = 0.25:                                        │
│   ─────────────────────                                         │
│   0kW  load → 50.00 Hz                                          │
│   2kW  load → 49.50 Hz                                          │
│   4kW  load → 49.00 Hz                                          │
│   6kW  load → 48.50 Hz                                          │
│                                                                 │
│   Lower frequency = more loaded = receives power from others    │
│   Higher frequency = less loaded = sends power to others        │
│                                                                 │
└─────────────────────────────────────────────────────────────────┘
```

---

## Learning Path

```
Part 1       Part 2        Part 3         Part 4          Parts 5-7
─────────────────────────────────────────────────────────────────────►

┌────────┐  ┌────────┐  ┌──────────┐  ┌───────────┐  ┌─────────────┐
│  LED   │  │ Safety │  │  500W    │  │  1kW →    │  │  Smart +    │
│Blinker │─►│   +    │─►│ Modified │─►│  2.5kW →  │─►│   Swarm     │
│26 proj │  │ MOSFET │  │ + Winding│  │  6-15kW   │  │  Microgrid  │
└────────┘  └────────┘  └──────────┘  └───────────┘  └─────────────┘
   9V         12V/20W      220V        OzInverter      4 households
```

**Power Progression (no dangerous gaps):**
```
9V → 12V/20W → 150W → 500W → 1kW → 2.5kW → 6-15kW → 20kW
```

---

## What You'll Build

| Part | Project | Power | Key Skills |
|:----:|---------|:-----:|------------|
| 1 | 26 fundamental projects | 9V | Soldering, Ohm's Law, transistors, 555, PWM |
| 2 | Safety + MOSFET Bridge | 12V | HV safety, first power MOSFETs |
| 3 | Modified Sine Inverter | 500W | H-bridge, IR2110, dead-time, winding |
| 4 | Pure Sine + OzInverter | 6-15kW | EG8010, MOSFET paralleling, thermal |
| 5 | Smart Upgrade | — | ESP32, CAN bus, Home Assistant |
| 6 | Swarm Microgrid | 4 houses | Droop control, power sharing |
| 7 | Libre Solar Integration | — | Open MPPT, BMS, ThingSet |

**Key Innovation:** 2.5kW intermediate build lets you practice MOSFET paralleling with $30 mistakes instead of $150 mistakes.

---

## Investment

| Milestone | Time | Cost |
|-----------|:----:|-----:|
| Single 6kW Inverter | 6-9 months | ~$1,230 |
| 20kW Parallel System | 12-18 months | ~$1,730 |
| 4-Household Microgrid | 18-24 months | ~$14,300 |

**Per household:** ~$3,575 (vs $10,000+ commercial equivalent)

**Savings:** 60-75% compared to Victron/SMA systems

---

## Repository Structure

```
curriculum/
├── part1_fundamentals.md              # 26 projects at safe 9V
├── part2_safety_and_mosfet_bridge.md  # HV safety + first MOSFETs
├── part3_modified_sine.md             # 150W → 500W + winding practice
├── part4_pure_sine.md                 # 1kW → 2.5kW → 6-15kW OzInverter
├── part5_smart_upgrade.md             # ESP32 + Home Assistant
├── part6_microgrid.md                 # Swarm architecture
└── part7_libre_solar.md               # Open source MPPT & BMS
```

---

## Quick Start

1. **[Part 1](curriculum/part1_fundamentals.md)** — Build 26 fundamental projects at safe 9V
2. **[Part 2](curriculum/part2_safety_and_mosfet_bridge.md)** — Learn HV safety + build first MOSFET circuit
3. **[Part 3](curriculum/part3_modified_sine.md)** — Build modified sine inverters (150W → 500W)
4. **[Part 4](curriculum/part4_pure_sine.md)** — Pure sine: 1kW → 2.5kW → 6-15kW OzInverter
5. **[Parts 5-7](curriculum/part5_smart_upgrade.md)** — Smart monitoring, microgrid, Libre Solar

---

## Safety

> ⚠️ **230V AC can kill. 48V DC can cause fires. Never work on live circuits.**

**Part 2 is mandatory** before any 220V work. It covers:
- Electrical safety fundamentals (30mA through heart = death)
- One-hand rule and safe work practices
- Capacitor discharge procedures
- Emergency response
- Safety quiz (must pass)

The curriculum uses incremental voltage progression: **9V → 12V → 220V**

---

## Hardware References

| Component | Source | Description |
|-----------|--------|-------------|
| OzInverter | [bryanhorology.com](https://bryanhorology.com/ozinverter.php) | 6kW+ inverter design |
| BMS-C1 | [Libre Solar](https://libre.solar) | 16S/100A battery management |
| MPPT-2420-HC | [Libre Solar](https://libre.solar) | 20A solar charge controller |
| ThingSet | [thingset.io](https://thingset.io) | Open communication protocol |
| HA Vibecode Agent | [GitHub](https://github.com/Coolver/home-assistant-vibecode-agent) | AI-assisted HA configuration |
| ESPHome JK-BMS | [GitHub](https://github.com/syssi/esphome-jk-bms) | JK BMS integration for HA |

---

## Why Swarm Architecture?

| Traditional | Swarm (Tiered Bus) |
|-------------|-------------------|
| Central controller (SPOF) | No central controller |
| All inverters must sync | Only 3 gateways sync on backbone |
| Complex wiring | Cluster isolation via contactors |
| Manual programming | Self-organizing via droop control |
| Proprietary protocols | Open CAN bus / ThingSet |

Each cluster operates independently most of the time. Gateways connect clusters only when power sharing is needed—like a flock of birds, no leader needed.

---

## License

Open source. Build for yourself, your community, or teach others.

---

<p align="center">
<strong>From zero electronics to community energy independence.</strong><br>
<em>Build it. Connect it. Power your village.</em>
</p>

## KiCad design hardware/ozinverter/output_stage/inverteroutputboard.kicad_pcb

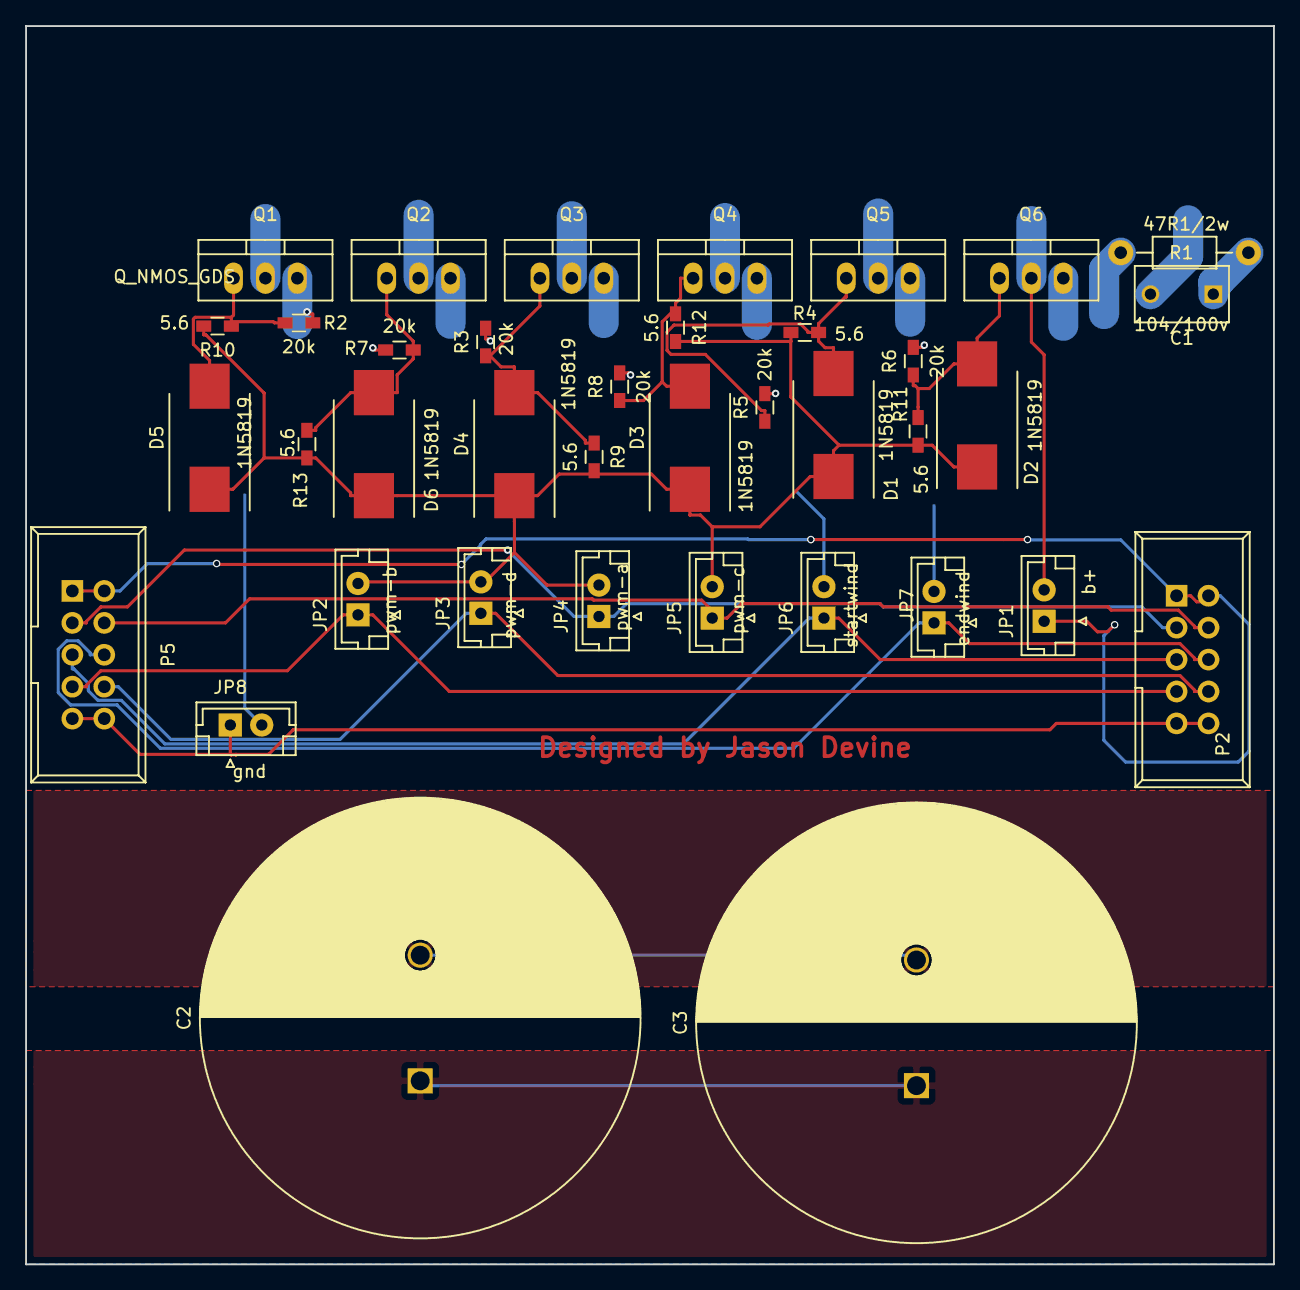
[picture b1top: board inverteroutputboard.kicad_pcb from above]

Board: 2 copper layers, 99.3 x 98.6 mm, 38 parts (0 on the bottom side), 20 nets.

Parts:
C1: 104/100v; C_Disc_D7.5_P5
C2, C3: CP; C_Radial_D35_L51_P10
D1, D2, D3, D4, D5, D6: 1N5819; DO-214AB_Handsoldering
JP1: b+; JST_EH_B02B-EH-A_02x2.50mm_Straight
JP2: pwm-b; JST_EH_B02B-EH-A_02x2.50mm_Straight
JP3: pwm-d; JST_EH_B02B-EH-A_02x2.50mm_Straight
JP4: pwm-a; JST_EH_B02B-EH-A_02x2.50mm_Straight
JP5: pwm-c; JST_EH_B02B-EH-A_02x2.50mm_Straight
JP6: startwind; JST_EH_B02B-EH-A_02x2.50mm_Straight
JP7: endwind; JST_EH_B02B-EH-A_02x2.50mm_Straight
JP8: gnd; JST_EH_B02B-EH-A_02x2.50mm_Straight
P2, P5: CONN_02X05; IDC_Header_Straight_10pins
Q1, Q2, Q3, Q4, Q5, Q6: Q_NMOS_GDS; TO-220_Neutral123_Vertical
R1: 47R1/2w; Resistor_Horizontal_RM10mm
R2, R3, R5, R6, R7, R8: 20k; R_0603_HandSoldering
R4, R9, R10, R11, R12, R13: 5.6; R_0603_HandSoldering

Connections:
/B+: JP1.1, P2.1, P2.2, P5.1, P5.2
/PWM-A: JP4.1, P2.3, P5.3
/PWM-B: JP2.1, P2.7, P5.7
/PWM-C: JP5.1, P2.4, P5.4
/PWM-D: JP3.1, P2.8, P5.8
/endwinding: JP7.1, P2.6, P5.6
/startwinding: JP6.1, P2.5, P5.5
GND: JP8.1, P2.9, P2.10, P5.9, P5.10
unnamed: C1.1, R1.1
unnamed: C1.2, JP1.2, Q1.2, Q2.2, Q3.2, Q4.2, Q5.2, Q6.2
unnamed: C2.1, C3.1
unnamed: C2.2, C3.2
unnamed: D1.1, D2.1, D3.1, D4.1, D5.1, D6.1, JP2.2, JP3.2, JP4.2, JP5.2, R4.2, R9.2, R10.2, R11.2, R12.2, R13.2
unnamed: D1.2, Q5.1, R4.1, R5.1
unnamed: D2.2, Q6.1, R6.1, R11.1
unnamed: D3.2, Q4.1, R8.1, R12.1
unnamed: D4.2, Q3.1, R3.1, R9.1
unnamed: D5.2, Q1.1, R2.1, R10.1
unnamed: D6.2, Q2.1, R7.1, R13.1
unnamed: JP6.2, JP7.2, JP8.2, Q1.3, Q2.3, Q3.3, Q4.3, Q5.3, Q6.3, R1.2, R2.2, R3.2, R5.2, R6.2, R7.2, R8.2

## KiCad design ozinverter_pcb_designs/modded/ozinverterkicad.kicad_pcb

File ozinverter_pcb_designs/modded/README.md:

# ozinvertermodded
This git is an opensource project. The orginal design comes from a bloke on Finders Island going by the handle of OZTULES.
He has given the design to the public domain. I have simply penned the schematic down by reverse engineering his PCB as this was not 
written down anywhere. The files here contain the basic version and also a version coming with switchmode regulators. Free for anyone to use.
4/09/16 reworked with switchmode ps for 48-12v conversion. Changed pcb to 10x10. Use this type of regulator http://www.ebay.com.au/itm/DC-DC-Converter-4-5-60V-Adjustable-Step-Down-Buck-LM2596HV-Power-Supply-Module-/261942503087?hash=item3cfcfd66af:g:pZwAAOSw-7RVE8oj

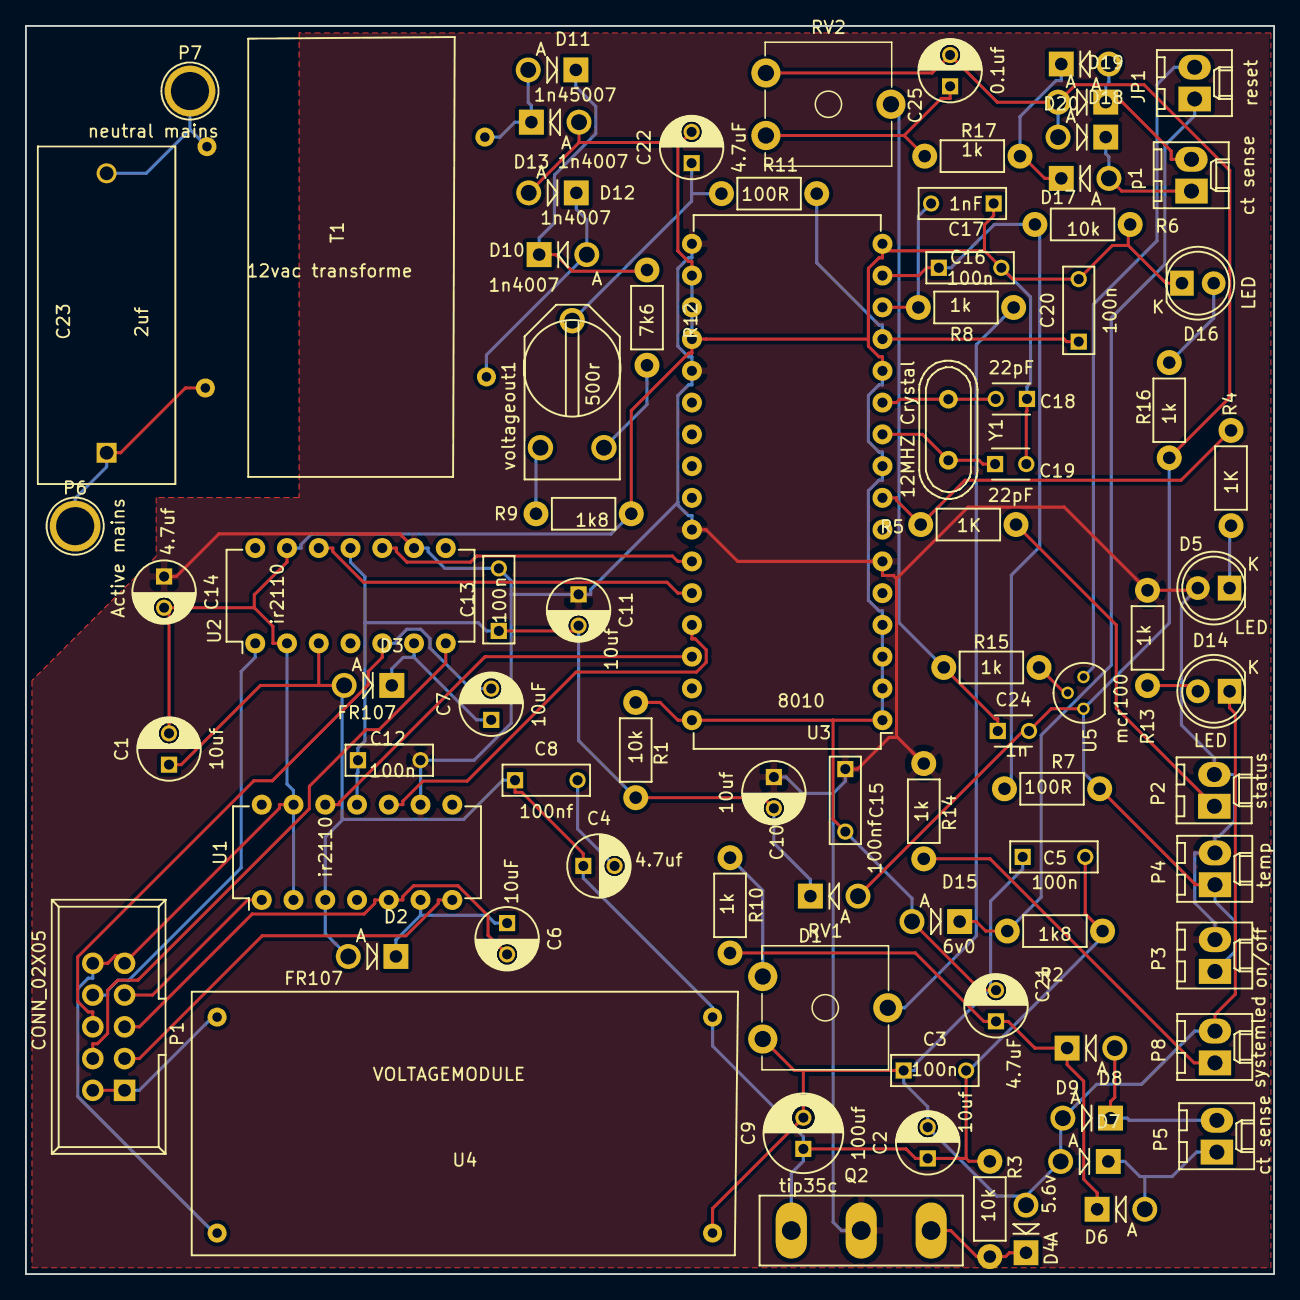
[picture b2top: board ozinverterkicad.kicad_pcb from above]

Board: 2 copper layers, 99.8 x 99.8 mm, 83 parts (0 on the bottom side), 52 nets.

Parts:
C1, C2: 10uf; C_Radial_D5_L6_P2.5
C3, C5, C12, C13, C16, C20: 100n; C_Rect_L7_W2.5_P5
C4, C14: 4.7uf; C_Radial_D5_L6_P2.5
C6, C7: 10uF; C_Radial_D5_L6_P2.5
C8, C15: 100nf; C_Rect_L7_W2.5_P5
C9: 100uf; C_Radial_D6.3_L11.2_P2.5
C10, C11: 10uf; C_Radial_D5_L11_P2.5
C17: 1nF; C_Rect_L7_W2.5_P5
C18, C19: 22pF; C_Disc_D3_P2.5
C21, C22: 4.7uF; C_Radial_D5_L6_P2.5
C23: 2uf; C_Rect_L27_W11_P22
C24: 1n; C_Disc_D3_P2.5
C25: 0.1uf; C_Radial_D5_L6_P2.5
D1, D6, D7, D8, D9, D17, D18, D19, D20: D; Diode_DO-41_SOD81_Vertical_AnodeUp
D2, D3: FR107; Diode_DO-41_SOD81_Vertical_AnodeUp
D4: 5.6v; Diode_DO-41_SOD81_Vertical_AnodeUp
D5, D14, D16: LED; LED-5MM
D10, D12, D13: 1n4007; Diode_DO-41_SOD81_Vertical_AnodeUp
D11: 1n45007; Diode_DO-41_SOD81_Vertical_AnodeUp
D15: 6v0; Diode_DO-41_SOD81_Vertical_AnodeUp
JP1: reset; Molex_KK-6410-02_02x2.54mm_Straight
P1: CONN_02X05; IDC_Header_Straight_10pins
P2: status; Molex_KK-6410-02_02x2.54mm_Straight
P3: on/off; Molex_KK-6410-02_02x2.54mm_Straight
P4: temp; Molex_KK-6410-02_02x2.54mm_Straight
P5: ct sense; Molex_KK-6410-02_02x2.54mm_Straight
P6: Active mains; 1pin
P7: neutral mains; 1pin
P8: systemled; Molex_KK-6410-02_02x2.54mm_Straight
Q2: tip35c; TO-247_Vertical_Neutral123
R1, R3, R6: 10k; Resistor_Horizontal_RM7mm
R2, R9: 1k8; Resistor_Horizontal_RM7mm
R4, R5: 1K; Resistor_Horizontal_RM7mm
R7, R11: 100R; Resistor_Horizontal_RM7mm
R8, R10, R13, R14, R15, R16, R17: 1k; Resistor_Horizontal_RM7mm
R12: 7k6; Resistor_Horizontal_RM7mm
RV1, RV2: 2k; Potentiometer_Trimmer_ACP_CA9v_Horizontal_Px10.0mm_Py5.0mm
T1: 12vac transforme; 3wtransformer
U1, U2: ir2110; DIP-14_W7.62mm
U3: 8010; DIP-32_W15.24mm
U4: VOLTAGEMODULE; lm2596hvsmodule
U5: mcr100; TO-92_Molded_Narrow
Y1: 12MHZ Crystal; Crystal_HC49-U_Vertical
p1: ct sense; Molex_KK-6410-02_02x2.54mm_Straight
voltageout1: 500r; RV2X4

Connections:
+5V: C10.1, C11.1, C12.2, C13.2, C14.1, C15.1, D5.2, P2.2, P3.2, P4.2, Q2.2, R13.1, R14.1, U1.9, U2.9, U3.6, U3.17, U3.21, U3.26
+12V: C1.1, C2.1, C3.2, C4.1, C5.2, C8.1, C9.1, D2.2, D3.2, Q2.3, R2.1, R3.1, U1.3, U2.3, U4.2
+48V: P1.1, P1.2, U4.3
GND: C1.2, C2.2, C3.1, C5.1, C9.2, C14.2, C15.2, C16.2, C17.1, C18.2, C19.1, C20.2, C21.2, C22.2, D4.2, D7.2, D8.2, D12.2, D13.2, D14.1, D15.2, D16.1, P1.9, P1.10, P8.2, R1.2, R6.2, R9.1, RV1.1, U1.2, U1.13, U2.2, U2.13, U3.1, U3.2, U3.3, U3.4, U3.9, U3.12, U3.16, U3.18, U3.19, U3.20, U3.32, U4.1, U4.4
unnamed: C4.2, C8.2
unnamed: C6.1, D2.1, U1.6
unnamed: C6.2, P1.5, U1.5
unnamed: C7.1, D3.1, U2.6
unnamed: C7.2, P1.6, U2.5
unnamed: C10.2, C11.2, C12.1, C13.1, D1.1, R1.1, U1.11, U2.11
unnamed: C16.1, R6.1, R7.2, U3.15
unnamed: C17.2, R8.2, U3.14
unnamed: C18.1, U3.10, Y1.2
unnamed: C19.2, U3.11, Y1.1
unnamed: C20.1, R11.1, U3.13
unnamed: C21.1, D6.1, D9.1, R10.1
unnamed: C22.1, R11.2, voltageout1.2
unnamed: C23.1, P6.1, T1.4
unnamed: C23.2, P7.1, T1.3
unnamed: C24.1, R15.1, RV2.2
unnamed: C24.2, C25.2, D1.2, D18.2, D19.2, P3.1, P4.1, R7.1, R16.1, RV2.3, U5.1
unnamed: C25.1, R17.2, RV2.1
unnamed: D4.1, Q2.1, R3.2
unnamed: D5.1, R4.2
unnamed: D6.2, D7.1, P5.1
unnamed: D8.1, D9.2, P5.2
unnamed: D10.1, D11.1, R12.1
unnamed: D10.2, D12.1, T1.2
unnamed: D11.2, D13.1, T1.1
unnamed: D14.2, R13.2
unnamed: D15.1, JP1.1, R2.2
unnamed: D16.2, R16.2
unnamed: D17.1, D20.1, R17.1
unnamed: D17.2, D18.1, p1.1
unnamed: D19.1, D20.2, p1.2
unnamed: JP1.2, U5.3
unnamed: P1.3, U1.7
unnamed: P1.4, U2.7
unnamed: P1.7, U1.1
unnamed: P1.8, U2.1
unnamed: P2.1, R5.2
unnamed: P8.1, R14.2
unnamed: R4.1, R5.1, U3.8
unnamed: R8.1, RV1.2
unnamed: R9.2, voltageout1.1
unnamed: R10.2, RV1.3
unnamed: R12.2, voltageout1.3
unnamed: R15.2, U5.2
unnamed: U1.10, U3.29
unnamed: U1.12, U3.30
unnamed: U2.10, U3.27
unnamed: U2.12, U3.28

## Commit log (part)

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2025-12-24 Fix index.md to match actual Part 1 project names
2025-12-24 Add practical device outcomes after each phase
2025-12-28 Remove gasifier - moving to separate repo
2026-01-18 Create WarpVerter: A Practical Build Guide
    # WarpVerter: A Practical Build Guide
2026-01-18 Rename WarpVerter: A Practical Build Guide to WarpVerter__APracticalBuildGuide.md
    File md
